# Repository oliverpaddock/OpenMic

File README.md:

# OpenMic
OpenMic is an open-source, 2-in, 2-out, usb-c audio interface.

## About

### Why open source?
Open source audio/music hardware is not scarce, but general-purpose open source audio interfaces for musicians are essentially non-existent. OpenMic brings repairability, transparency, and education to an overlooked corner of music hardware.

You own your hardware. All schematics, firmware, and design files are publicly accessible so you can repair it, modify it, and understand it.

### What is OpenMic?
If you aren't familiar with audio interfaces like the [Focusrite Scarlett 2i2](https://us.focusrite.com/products/scarlett-2i2) or the [Universal Audio Apollo Twin](https://www.uaudio.com/products/apollo-twin-x), they basically take analog audio - from a microphone, a guitar, a synth, etc. - and convert it into digital audio your computer can use in a DAW like Ableton, Logic, or Audacity. They also convert digital audio from your computer back into analog audio that you can hear through speakers or headphones. Interfaces also typically provide some sort of amplification or volume control on the inputs and outputs.

This is exactly what OpenMic does. Two inputs that can take microphone/line/instrument level signals, outputs for your speakers, and a headphone jack. Plus a few other features like phantom power that are listed in more detail in the [Features](#features) section.

*System block diagram*

## Current Status
OpenMic is currently in the prototyping stage. The circuit has been designed and [simulated](hardware/sims/), and individual systems are being built and tested. View the [schematics](docs/schematics/openmic.pdf) to see the current circuit design.

Progress will be posted on the [OpenMic blog](https://olpad.codeberg.page/openmic-blog) as prototyping continues.

### Roadmap
- [x] Initial design and component selection
- [x] Simulation for design verification
- [ ] Subsystem prototyping
- [ ] Full board design in KiCad
- [ ] First full v1 board
- [ ] Crowd supply launch
- [ ] Production

## Features
- 2 combo XLR/TRS inputs (mic/line/inst)
- Balanced TRS stereo line outputs
- TRS headphone output
- 48V phantom power
- Direct monitoring
- Up to 32-bit/96kHz
- USB-C bus powered (1.5A) with external USB-C fallback
- Drives headphones from 32Ω to 600Ω
- Fully open hardware and firmware

## Getting Started
If you want to view/edit KiCAD files, make sure to add the part libraries located in /hardware/libs to your project or globally in your KiCAD instance.

---

### Sponsors

&emsp;

&emsp;

### Special Thanks

THAT Corporation

Neutrik

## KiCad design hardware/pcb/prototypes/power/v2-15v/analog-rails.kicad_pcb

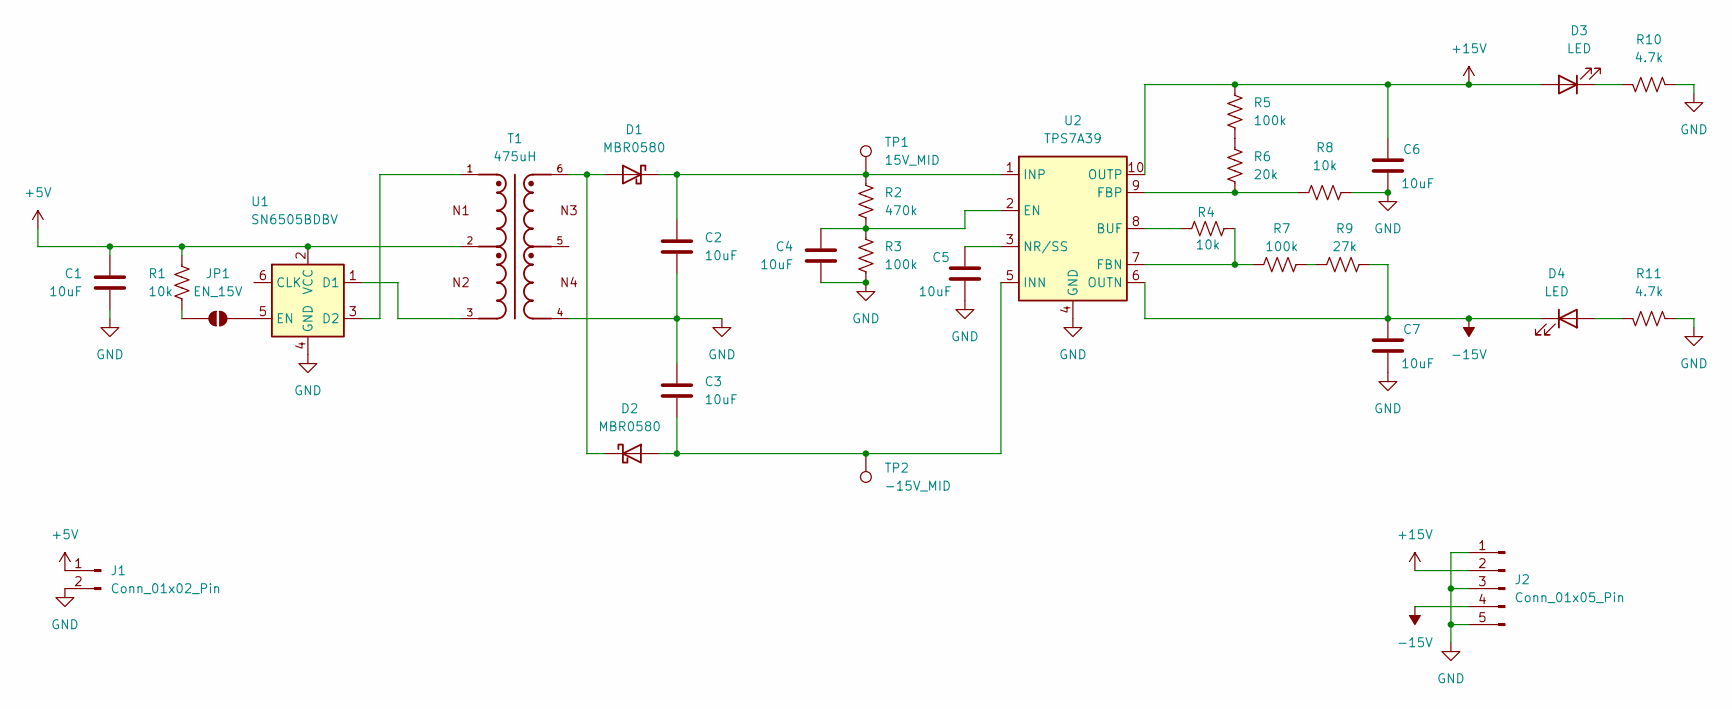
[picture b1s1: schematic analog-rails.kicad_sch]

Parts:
C1, C5: 10uF; C_0805_2012Metric_Pad1.18x1.45mm_HandSolder; Voltage 10; MPN CL21A106KAYNNNE; LCSC C15850
C2, C3, C4, C6, C7: 10uF; C_0805_2012Metric_Pad1.18x1.45mm_HandSolder; Voltage 50; MPN CL21A106KAYNNNE; LCSC C15850
D1, D2: MBR0580; D_SOD-123; MPN MBR0580; LCSC C77339
D3, D4: LED; LED_0805_2012Metric_Pad1.15x1.40mm_HandSolder
J1: Conn_01x02_Pin; PinHeader_1x02_P2.54mm_Vertical
J2: Conn_01x05_Pin; PinHeader_1x05_P2.54mm_Vertical
JP1: EN_15V; SolderJumper-2_P1.3mm_Open_RoundedPad1.0x1.5mm
R1, R4, R8: 10k; R_0805_2012Metric_Pad1.20x1.40mm_HandSolder; MPN 0805W8F1002T5E; LCSC C17414
R2: 470k; R_0805_2012Metric_Pad1.20x1.40mm_HandSolder; MPN 0805W8F4700T5E; LCSC C17710
R3, R5, R7: 100k; R_0805_2012Metric_Pad1.20x1.40mm_HandSolder; MPN 0805W8F1003T5E; LCSC C149504
R6: 20k; R_0805_2012Metric_Pad1.20x1.40mm_HandSolder; MPN 0805W8F2002T5E; LCSC C4328
R9: 27k; R_0805_2012Metric_Pad1.20x1.40mm_HandSolder; MPN 0805W8F2702T5E; LCSC C17593
R10, R11: 4.7k; R_0805_2012Metric_Pad1.20x1.40mm_HandSolder; MPN 0805W8F1003T5E; LCSC C149504
T1: 475uH; Wurth Elektronik 760390015; MPN 760390015; LCSC C249186
TP1: 15V_MID; TestPoint_Pad_1.0x1.0mm
TP2: -15V_MID; TestPoint_Pad_1.0x1.0mm
U1: SN6505BDBV; SOT-23-6; MPN SN6505BDBVR; LCSC C74518
U2: TPS7A39; Texas_S-PVSON-N10_ThermalVias; MPN TPS7A3901DSCR; LCSC C2685819

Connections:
+5V: C1.1, J1.1, R1.2, T1.2, U1.2 (VCC)
+15V: C6.1, D3.2 (A), J2.2, R5.1, U2.10 (OUTP)
-15V: C7.1, D4.1 (K), J2.4, R9.2, U2.6 (OUTN)
GND: C1.2, C2.2, C3.1, C4.2, C5.2, C6.2, C7.2, J1.2, J2.1, J2.3, J2.5, R3.2, R8.2, R10.1, R11.1, T1.4, U1.4 (GND), U2.4 (GND), U2.11 (GND)
unnamed: D1.2 (A), D2.1 (K), T1.6
unnamed: C2.1, D1.1 (K), R2.1, TP1.1 (1_1), U2.1 (INP)
unnamed: C3.2, D2.2 (A), TP2.1 (1_1), U2.5 (INN)
unnamed: D3.1 (K), R10.2
unnamed: D4.2 (A), R11.2
unnamed: JP1.1 (A), R1.1
unnamed: JP1.2 (B), U1.5 (EN)
unnamed: R5.2, R6.1
unnamed: R7.2, R9.1
unnamed: T1.3, U1.1 (D1)
unnamed: T1.1, U1.3 (D2)
unnamed: R4.1, U2.8 (BUF)
unnamed: C4.1, R2.2, R3.1, U2.2 (EN)
unnamed: R4.2, R7.1, U2.7 (FBN)
unnamed: R6.2, R8.1, U2.9 (FBP)
unnamed: C5.1, U2.3 (NR/SS)

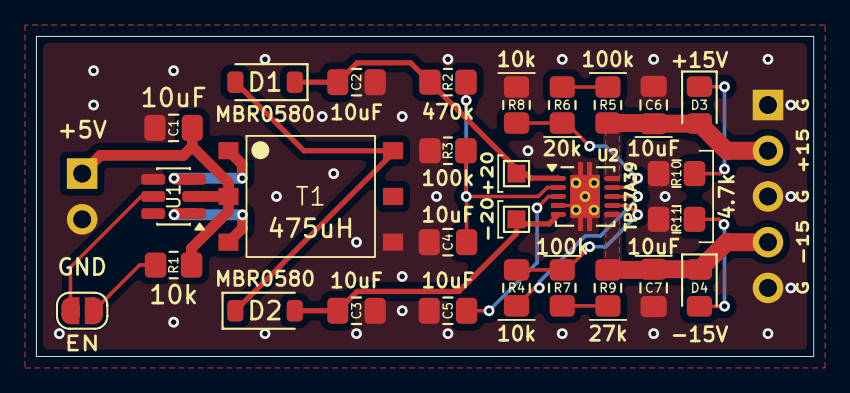
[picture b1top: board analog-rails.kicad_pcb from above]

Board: 2 copper layers, 43.2 x 17.8 mm, 30 parts (0 on the bottom side), 20 nets.

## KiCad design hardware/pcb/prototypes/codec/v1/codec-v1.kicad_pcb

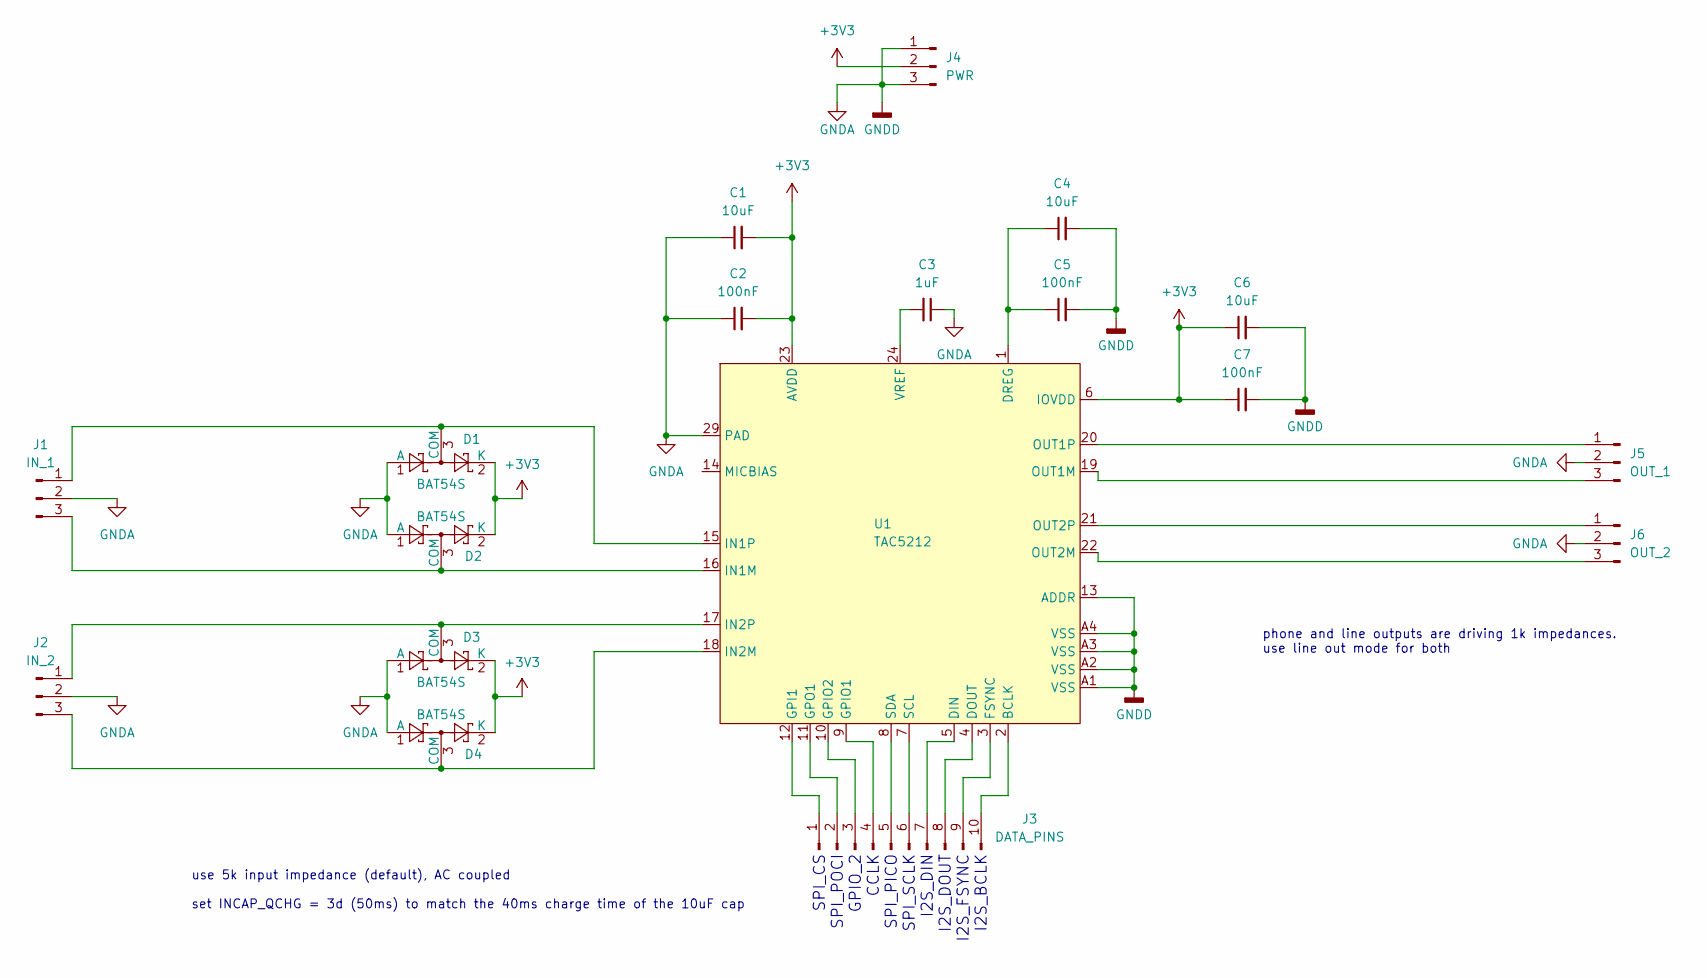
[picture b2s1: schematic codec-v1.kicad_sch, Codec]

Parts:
C1, C4, C6: 10uF; C_0805_2012Metric
C2, C5, C7: 100nF; C_0805_2012Metric
C3: 1uF; C_0805_2012Metric
D1, D2, D3, D4: BAT54S; SOT-23
J1: IN_1; PinHeader_1x03_P2.54mm_Vertical
J2: IN_2; PinHeader_1x03_P2.54mm_Vertical
J3: DATA_PINS; PinHeader_1x10_P2.54mm_Vertical
J4: PWR; PinHeader_1x03_P2.54mm_Vertical
J5: OUT_1; PinHeader_1x03_P2.54mm_Vertical
J6: OUT_2; PinHeader_1x03_P2.54mm_Vertical
U1: TAC5212

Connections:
+3V3: C1.2, C2.2, C6.1, C7.1, D1.2 (K), D2.2 (K), D3.2 (K), D4.2 (K), J4.2, U1.6 (IOVDD), U1.23 (AVDD)
GNDA: C1.1, C2.1, C3.1, C4.2, C5.2, C6.2, C7.2, D1.1 (A), D2.1 (A), D3.1 (A), D4.1 (A), J1.2, J2.2, J4.1, J4.3, J5.2, J6.2, U1.13 (ADDR), U1.29 (PAD), U1.A1 (VSS), U1.A2 (VSS), U1.A3 (VSS), U1.A4 (VSS)
unnamed: D1.3 (COM), J1.1, U1.15 (IN1P)
unnamed: D2.3 (COM), J1.3, U1.16 (IN1M)
unnamed: D3.3 (COM), J2.1, U1.17 (IN2P)
unnamed: D4.3 (COM), J2.3, U1.18 (IN2M)
unnamed: J3.1, U1.12 (GPI1)
unnamed: J3.2, U1.11 (GPO1)
unnamed: J3.3, U1.10 (GPIO2)
unnamed: J3.4, U1.9 (GPIO1)
unnamed: J3.5, U1.8 (SDA)
unnamed: J3.6, U1.7 (SCL)
unnamed: J3.7, U1.5 (DIN)
unnamed: J3.8, U1.4 (DOUT)
unnamed: J3.9, U1.3 (FSYNC)
unnamed: J3.10, U1.2 (BCLK)
unnamed: J5.1, U1.20 (OUT1P)
unnamed: J5.3, U1.19 (OUT1M)
unnamed: J6.1, U1.21 (OUT2P)
unnamed: J6.3, U1.22 (OUT2M)
unnamed: C4.1, C5.1, U1.1 (DREG)
unnamed: C3.2, U1.24 (VREF)

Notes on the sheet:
phone and line outputs are driving 1k impedances. use line out mode for both
SPI_CS SPI_POCI GPIO_2 CCLK SPI_PICO SPI_SCLK I2S_DIN I2S_DOUT I2S_FSYNC I2S_BCLK
use 5k input impedance (default), AC coupled set INCAP_QCHG = 3d (50ms) to match the 40ms charge time of the 10uF cap

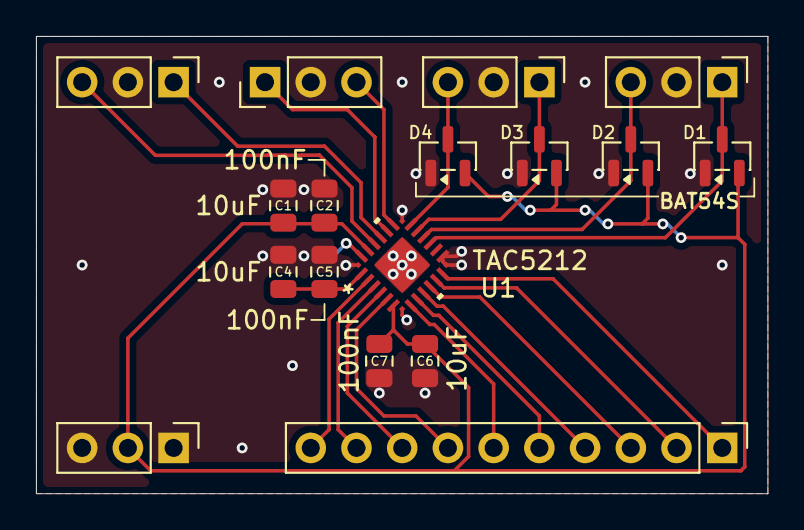
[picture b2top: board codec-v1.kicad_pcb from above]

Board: 2 copper layers, 40.6 x 25.4 mm, 18 parts (1 on the bottom side), 22 nets.

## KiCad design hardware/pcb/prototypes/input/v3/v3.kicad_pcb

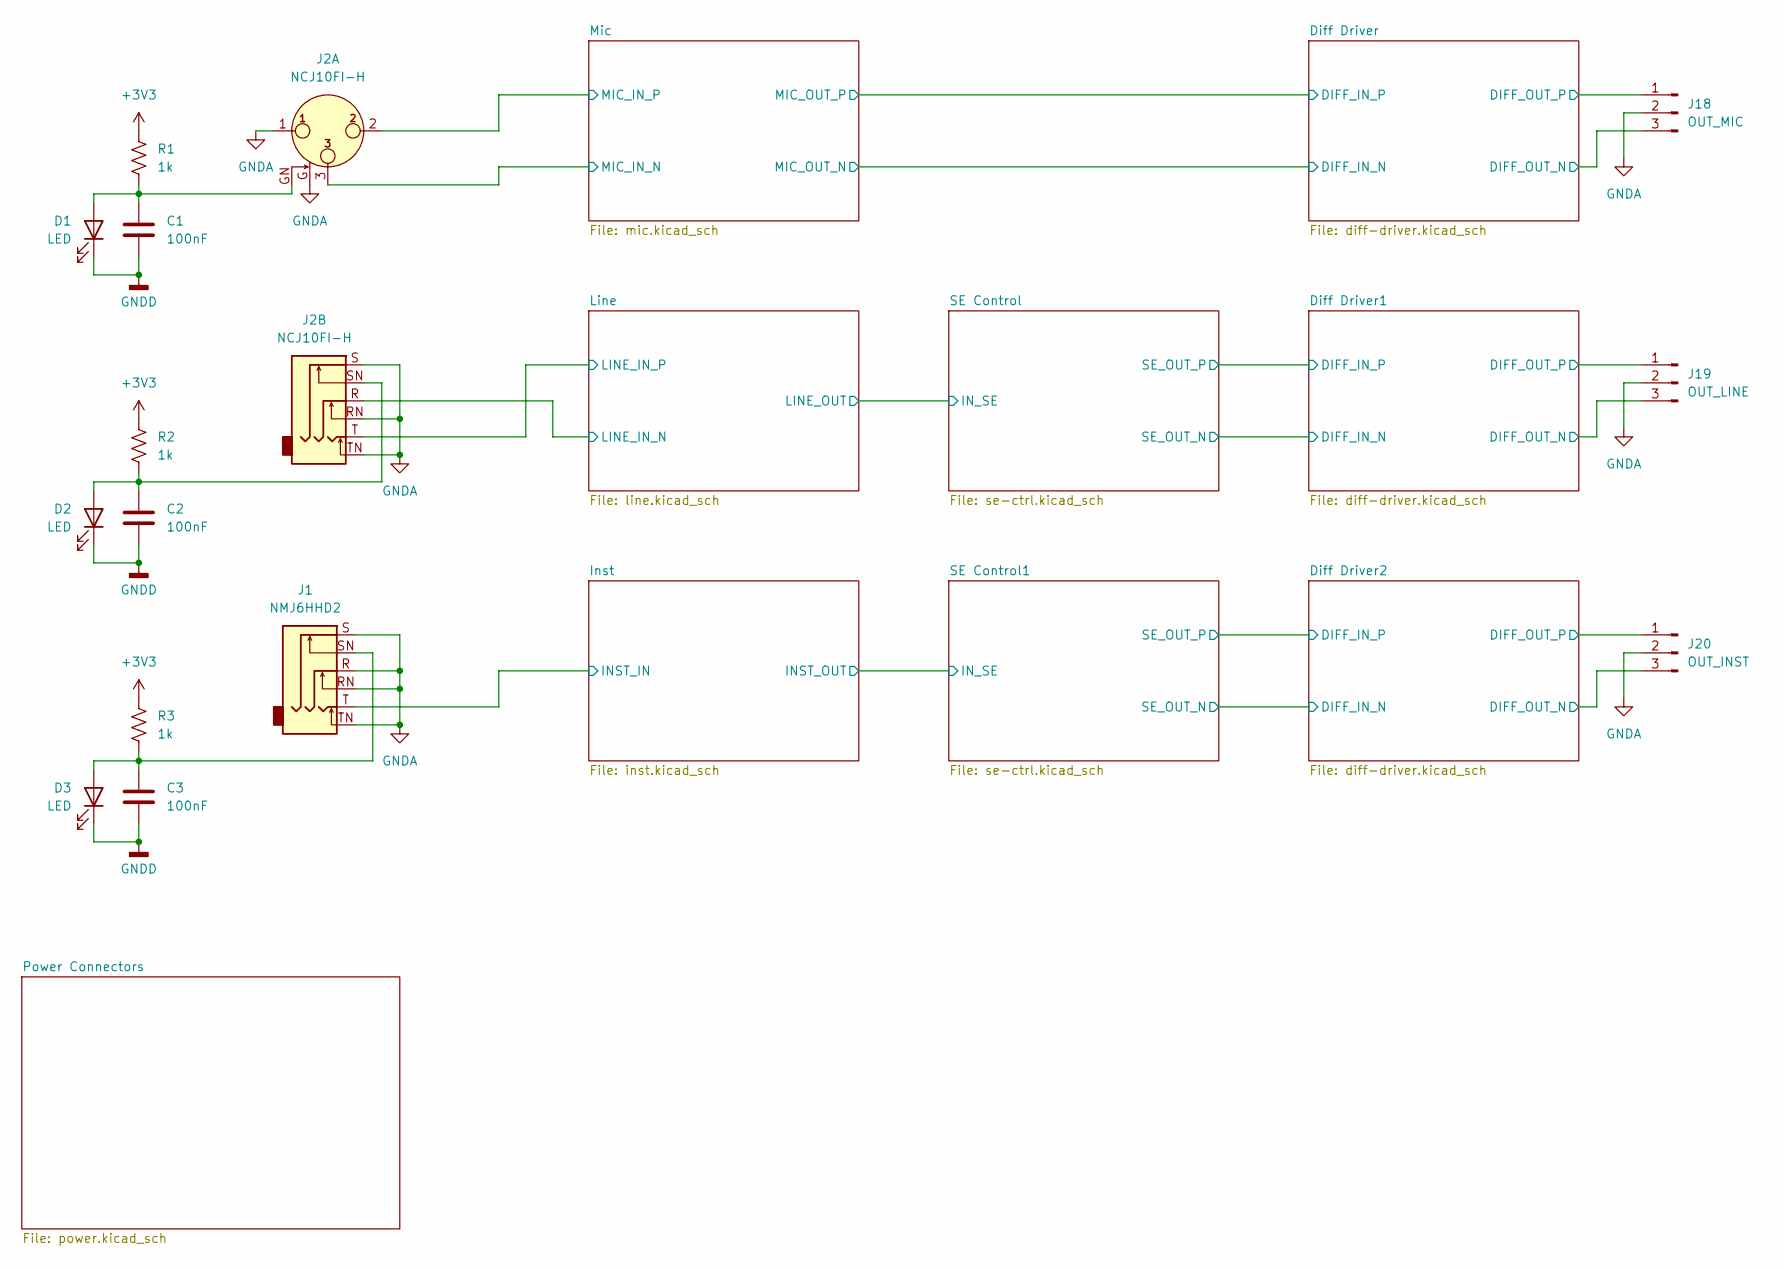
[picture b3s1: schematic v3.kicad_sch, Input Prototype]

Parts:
C1, C2, C3: 100nF; C_0805_2012Metric_Pad1.18x1.45mm_HandSolder; Voltage 6
D1, D2, D3: LED; LED_0805_2012Metric_Pad1.15x1.40mm_HandSolder
J1: NMJ6HHD2; Jack_6.35mm_Neutrik_NMJ6HHD2_Horizontal
J2: NCJ10FI-H; Jack_XLR-6.35mm_Neutrik_NCJ10FI-H_Horizontal
J18: OUT_MIC; PinHeader_1x03_P2.54mm_Vertical
J19: OUT_LINE; PinHeader_1x03_P2.54mm_Vertical
J20: OUT_INST; PinHeader_1x03_P2.54mm_Vertical
R1, R2, R3: 1k; R_0805_2012Metric_Pad1.20x1.40mm_HandSolder

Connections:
+3V3: R1.1, R2.1, R3.1; also elsewhere on the board
/Diff Driver1/DIFF_OUT_N: J19.3; also elsewhere on the board
/Diff Driver1/DIFF_OUT_P: J19.1; also elsewhere on the board
/Diff Driver2/DIFF_OUT_N: J20.3; also elsewhere on the board
/Diff Driver2/DIFF_OUT_P: J20.1; also elsewhere on the board
/Diff Driver/DIFF_OUT_N: J18.3; also elsewhere on the board
/Diff Driver/DIFF_OUT_P: J18.1; also elsewhere on the board
/Inst/INST_IN: J1.T; also elsewhere on the board
/Line/LINE_IN_N: J2.R; also elsewhere on the board
/Line/LINE_IN_P: J2.T; also elsewhere on the board
/Mic/MIC_IN_N: J2.3; also elsewhere on the board
/Mic/MIC_IN_P: J2.2; also elsewhere on the board
Earth: C1.2, C2.2, C3.2, D1.1 (K), D2.1 (K), D3.1 (K), J1.R, J1.RN, J1.S, J1.TN, J2.1, J2.G, J2.RN, J2.S, J2.TN, J18.2, J19.2, J20.2; also elsewhere on the board
unnamed: C1.1, D1.2 (A), J2.GN, R1.2
unnamed: C2.1, D2.2 (A), J2.SN, R2.2
unnamed: C3.1, D3.2 (A), J1.SN, R3.2

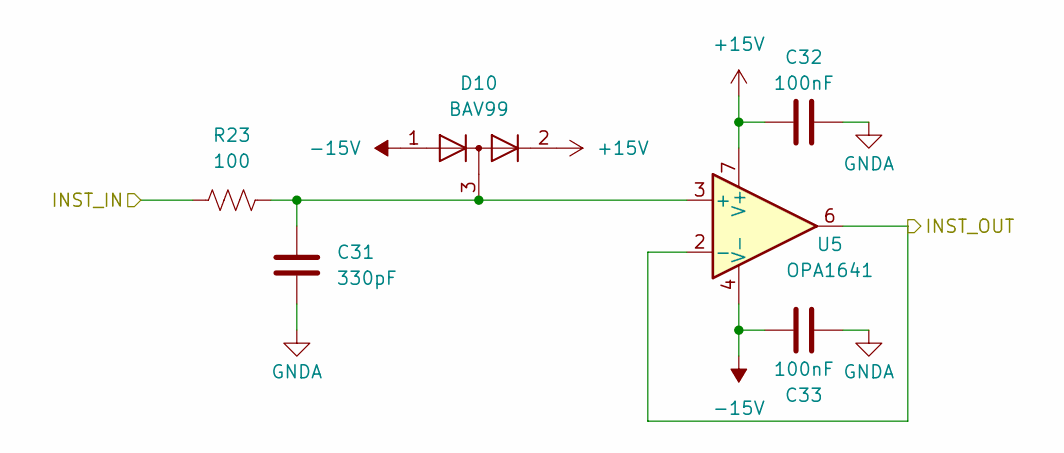
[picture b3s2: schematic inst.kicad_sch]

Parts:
C31: 330pF; C_0805_2012Metric_Pad1.18x1.45mm_HandSolder; Voltage 6
C32, C33: 100nF; C_0805_2012Metric_Pad1.18x1.45mm_HandSolder; Voltage 50
D10: BAV99; SOT-23
R23: 100; R_0805_2012Metric_Pad1.20x1.40mm_HandSolder
U5: OPA1641; SOIC-8_3.9x4.9mm_P1.27mm

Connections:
+15V: C32.2, D10.2 (A), U5.7 (V+); also elsewhere on the board
-15V: C33.2, D10.1 (K), U5.4 (V-); also elsewhere on the board
/Inst/INST_IN: R23.2; also elsewhere on the board
/Inst/INST_OUT: U5.2 (-), U5.6; also elsewhere on the board
Earth: C31.2, C32.1, C33.1; also elsewhere on the board
unnamed: C31.1, D10.3 (K), R23.1, U5.3 (+)

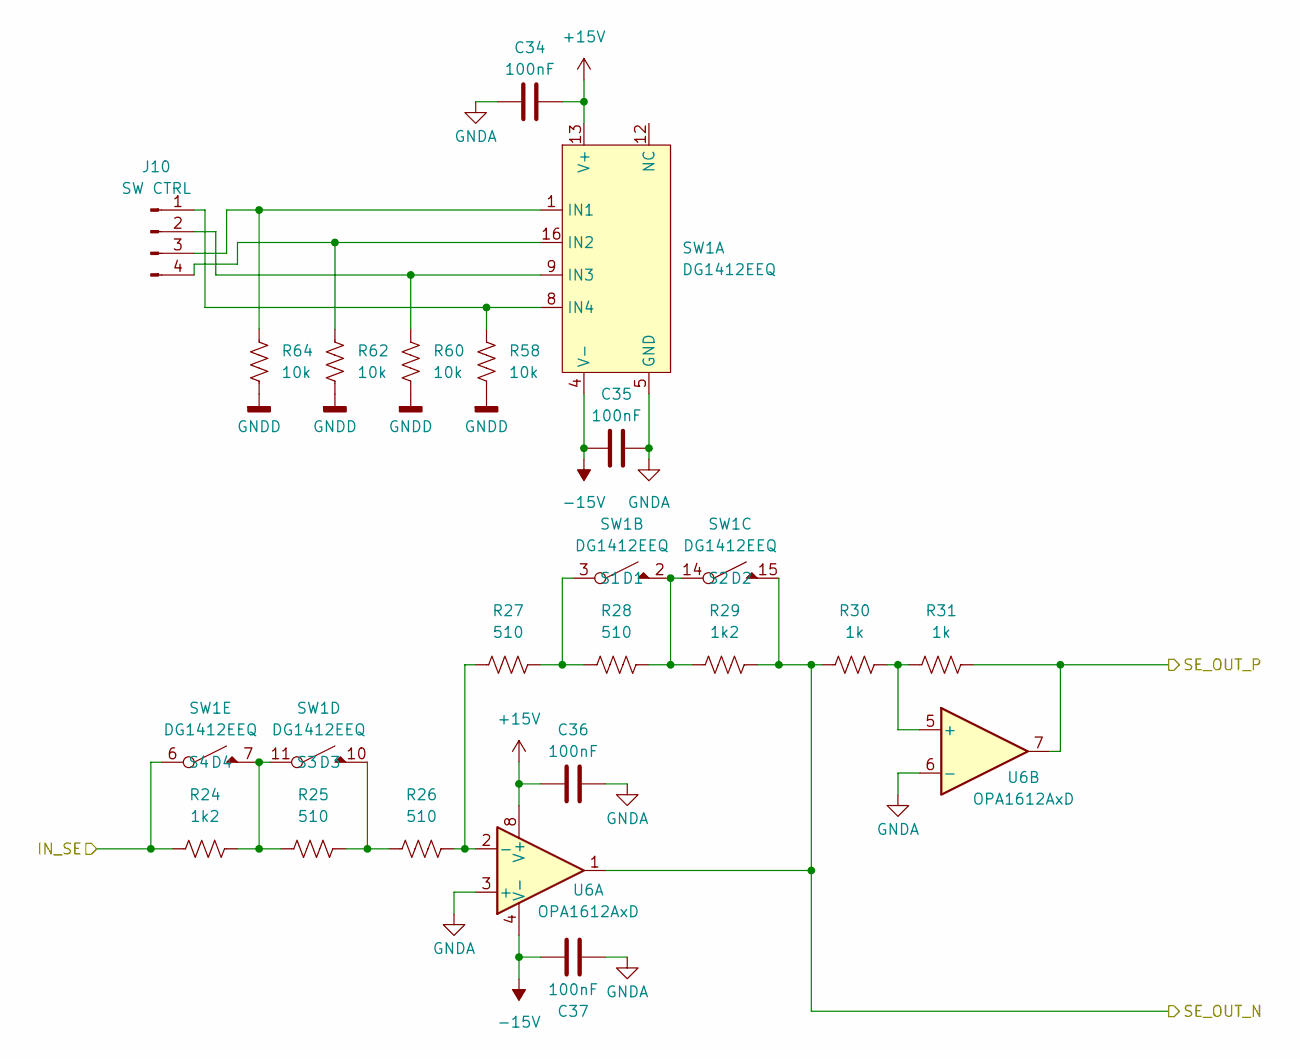
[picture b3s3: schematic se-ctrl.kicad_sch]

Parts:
C34, C35, C36, C37: 100nF; C_0805_2012Metric_Pad1.18x1.45mm_HandSolder; Voltage 50
J10: SW CTRL; PinHeader_1x04_P2.54mm_Vertical
R24, R29: 1k2; R_0805_2012Metric_Pad1.20x1.40mm_HandSolder
R25, R26, R27, R28: 510; R_0805_2012Metric_Pad1.20x1.40mm_HandSolder
R30, R31: 1k; R_0805_2012Metric_Pad1.20x1.40mm_HandSolder
R58, R60, R62, R64: 10k; R_0805_2012Metric_Pad1.20x1.40mm_HandSolder
SW1: DG1412EEQ; TSSOP-16_4.4x5mm_P0.65mm
U6: OPA1612AxD; SOIC-8_3.9x4.9mm_P1.27mm

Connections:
+15V: C34.2, C36.2, SW1.13 (V+), U6.8 (V+); also elsewhere on the board
-15V: C35.2, C37.2, SW1.4 (V-), U6.4 (V-); also elsewhere on the board
/Diff Driver1/DIFF_IN_N: R29.1, R30.2, SW1.15 (D2), U6.1; also elsewhere on the board
/Diff Driver1/DIFF_IN_P: R31.1, U6.7; also elsewhere on the board
/Line/LINE_OUT: R24.2, SW1.6 (S4); also elsewhere on the board
Earth: C34.1, C35.1, C36.1, C37.1, R58.2, R60.2, R62.2, R64.2, SW1.5 (GND), U6.3 (+), U6.6 (-); also elsewhere on the board
unnamed: J10.1, R58.1, SW1.8 (IN4)
unnamed: J10.2, R60.1, SW1.9 (IN3)
unnamed: J10.3, R64.1, SW1.1 (IN1)
unnamed: J10.4, R62.1, SW1.16 (IN2)
unnamed: R28.1, R29.2, SW1.2 (D1), SW1.14 (S2)
unnamed: R27.1, R28.2, SW1.3 (S1)
unnamed: R25.1, R26.2, SW1.10 (D3)
unnamed: R24.1, R25.2, SW1.7 (D4), SW1.11 (S3)
unnamed: R26.1, R27.2, U6.2 (-)
unnamed: R30.1, R31.2, U6.5 (+)

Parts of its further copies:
C38, C39, C40, C41: 100nF; C_0805_2012Metric_Pad1.18x1.45mm_HandSolder; Voltage 50
J11: SW CTRL; PinHeader_1x04_P2.54mm_Vertical
R32, R37: 1k2; R_0805_2012Metric_Pad1.20x1.40mm_HandSolder
R33, R34, R35, R36: 510; R_0805_2012Metric_Pad1.20x1.40mm_HandSolder
R38, R39: 1k; R_0805_2012Metric_Pad1.20x1.40mm_HandSolder
R59, R61, R63, R65: 10k; R_0805_2012Metric_Pad1.20x1.40mm_HandSolder
SW2: DG1412EEQ; TSSOP-16_4.4x5mm_P0.65mm
U7: OPA1612AxD; SOIC-8_3.9x4.9mm_P1.27mm

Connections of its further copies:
+15V: C38.2, C40.2, SW2.13 (V+), U7.8 (V+); also elsewhere on the board
-15V: C39.2, C41.2, SW2.4 (V-), U7.4 (V-); also elsewhere on the board
/Diff Driver2/DIFF_IN_N: R37.1, R38.2, SW2.15 (D2), U7.1; also elsewhere on the board
/Diff Driver2/DIFF_IN_P: R39.1, U7.7; also elsewhere on the board
/Inst/INST_OUT: R32.2, SW2.6 (S4); also elsewhere on the board
Earth: C38.1, C39.1, C40.1, C41.1, R59.2, R61.2, R63.2, R65.2, SW2.5 (GND), U7.3 (+), U7.6 (-); also elsewhere on the board
unnamed: J11.1, R59.1, SW2.8 (IN4)
unnamed: J11.2, R61.1, SW2.9 (IN3)
unnamed: J11.3, R65.1, SW2.1 (IN1)
unnamed: J11.4, R63.1, SW2.16 (IN2)
unnamed: R36.1, R37.2, SW2.2 (D1), SW2.14 (S2)
unnamed: R35.1, R36.2, SW2.3 (S1)
unnamed: R33.1, R34.2, SW2.10 (D3)
unnamed: R32.1, R33.2, SW2.7 (D4), SW2.11 (S3)
unnamed: R34.1, R35.2, U7.2 (-)
unnamed: R38.1, R39.2, U7.5 (+)

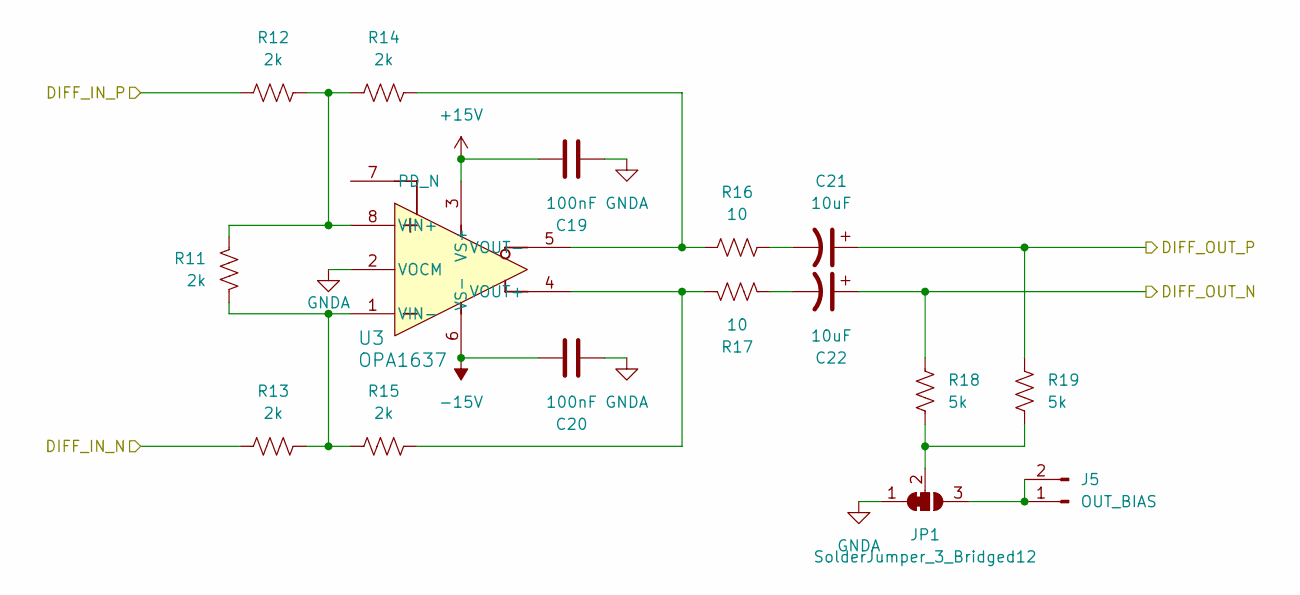
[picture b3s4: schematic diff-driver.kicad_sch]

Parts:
C19, C20: 100nF; C_0805_2012Metric_Pad1.18x1.45mm_HandSolder; Voltage 6
C21, C22: 10uF; C_Radial_D5.0mm_H11.0mm_P2.00mm; Voltage 50
J5: OUT_BIAS; PinHeader_1x02_P2.54mm_Vertical
JP1: SolderJumper_3_Bridged12; SolderJumper-3_P1.3mm_Bridged12_RoundedPad1.0x1.5mm
R11, R12, R13, R14, R15: 2k; R_0805_2012Metric_Pad1.20x1.40mm_HandSolder
R16, R17: 10; R_0805_2012Metric_Pad1.20x1.40mm_HandSolder
R18, R19: 5k; R_0805_2012Metric_Pad1.20x1.40mm_HandSolder
U3: OPA1637; VSSOP-8_3x3mm_P0.65mm

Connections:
+15V: C19.1, U3.3 (VS+); also elsewhere on the board
-15V: C20.1, U3.6 (VS-); also elsewhere on the board
/Diff Driver/DIFF_IN_N: R13.1; also elsewhere on the board
/Diff Driver/DIFF_IN_P: R12.1; also elsewhere on the board
/Diff Driver/DIFF_OUT_N: C22.1, R18.2; also elsewhere on the board
/Diff Driver/DIFF_OUT_P: C21.1, R19.2; also elsewhere on the board
Earth: C19.2, C20.2, JP1.1 (A), U3.2 (VOCM); also elsewhere on the board
unnamed: C21.2, R16.2
unnamed: C22.2, R17.2
unnamed: J5.1, J5.2, JP1.3 (B)
unnamed: JP1.2 (C), R18.1, R19.1
unnamed: R11.2, R12.2, R14.1, U3.8 (VIN+)
unnamed: R11.1, R13.2, R15.1, U3.1 (VIN-)
unnamed: R15.2, R17.1, U3.4 (VOUT+)
unnamed: R14.2, R16.1, U3.5 (VOUT-)

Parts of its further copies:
C42, C43, C46, C47: 100nF; C_0805_2012Metric_Pad1.18x1.45mm_HandSolder; Voltage 6
C44, C45, C48, C49: 10uF; C_Radial_D5.0mm_H11.0mm_P2.00mm; Voltage 50
J12, J13: OUT_BIAS; PinHeader_1x02_P2.54mm_Vertical
JP2, JP3: SolderJumper_3_Bridged12; SolderJumper-3_P1.3mm_Bridged12_RoundedPad1.0x1.5mm
R40, R41, R42, R43, R44, R49, R50, R51, R52, R53: 2k; R_0805_2012Metric_Pad1.20x1.40mm_HandSolder
R45, R46, R54, R55: 10; R_0805_2012Metric_Pad1.20x1.40mm_HandSolder
R47, R48, R56, R57: 5k; R_0805_2012Metric_Pad1.20x1.40mm_HandSolder
U8, U9: OPA1637; VSSOP-8_3x3mm_P0.65mm

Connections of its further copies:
+15V: C42.1, C46.1, U8.3 (VS+), U9.3 (VS+); also elsewhere on the board
-15V: C43.1, C47.1, U8.6 (VS-), U9.6 (VS-); also elsewhere on the board
/Diff Driver1/DIFF_IN_N: R42.1; also elsewhere on the board
/Diff Driver1/DIFF_IN_P: R41.1; also elsewhere on the board
/Diff Driver1/DIFF_OUT_N: C45.1, R47.2; also elsewhere on the board
/Diff Driver1/DIFF_OUT_P: C44.1, R48.2; also elsewhere on the board
/Diff Driver2/DIFF_IN_N: R51.1; also elsewhere on the board
/Diff Driver2/DIFF_IN_P: R50.1; also elsewhere on the board
/Diff Driver2/DIFF_OUT_N: C49.1, R56.2; also elsewhere on the board
/Diff Driver2/DIFF_OUT_P: C48.1, R57.2; also elsewhere on the board
Earth: C42.2, C43.2, C46.2, C47.2, JP2.1 (A), JP3.1 (A), U8.2 (VOCM), U9.2 (VOCM); also elsewhere on the board
unnamed: C44.2, R45.2
unnamed: C45.2, R46.2
unnamed: C48.2, R54.2
unnamed: C49.2, R55.2
unnamed: J12.1, J12.2, JP2.3 (B)
unnamed: J13.1, J13.2, JP3.3 (B)
unnamed: JP2.2 (C), R47.1, R48.1
unnamed: JP3.2 (C), R56.1, R57.1
unnamed: R40.2, R41.2, R43.1, U8.8 (VIN+)
unnamed: R40.1, R42.2, R44.1, U8.1 (VIN-)
unnamed: R44.2, R46.1, U8.4 (VOUT+)
unnamed: R43.2, R45.1, U8.5 (VOUT-)
unnamed: R49.2, R50.2, R52.1, U9.8 (VIN+)
unnamed: R49.1, R51.2, R53.1, U9.1 (VIN-)
unnamed: R53.2, R55.1, U9.4 (VOUT+)
unnamed: R52.2, R54.1, U9.5 (VOUT-)

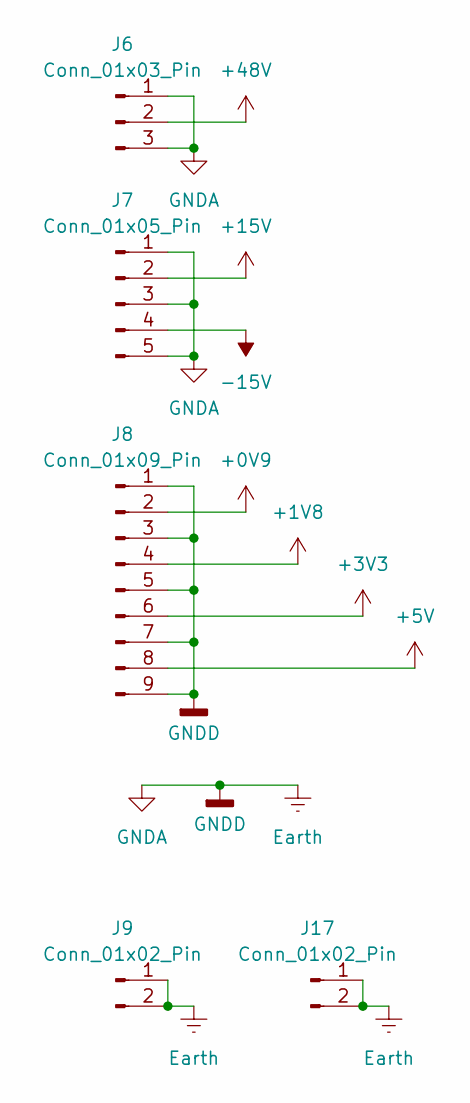
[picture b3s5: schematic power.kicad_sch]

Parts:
J6: Conn_01x03_Pin; PinHeader_1x03_P2.54mm_Vertical
J7: Conn_01x05_Pin; PinHeader_1x05_P2.54mm_Vertical
J8: Conn_01x09_Pin; PinHeader_1x09_P2.54mm_Vertical
J9, J17: Conn_01x02_Pin; PinHeader_1x02_P2.54mm_Vertical

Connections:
+0V9: J8.2
+1V8: J8.4
+3V3: J8.6; also elsewhere on the board
+5V: J8.8
+15V: J7.2; also elsewhere on the board
+48V: J6.2; also elsewhere on the board
-15V: J7.4; also elsewhere on the board
Earth: J6.1, J6.3, J7.1, J7.3, J7.5, J8.1, J8.3, J8.5, J8.7, J8.9, J9.1, J9.2, J17.1, J17.2; also elsewhere on the board

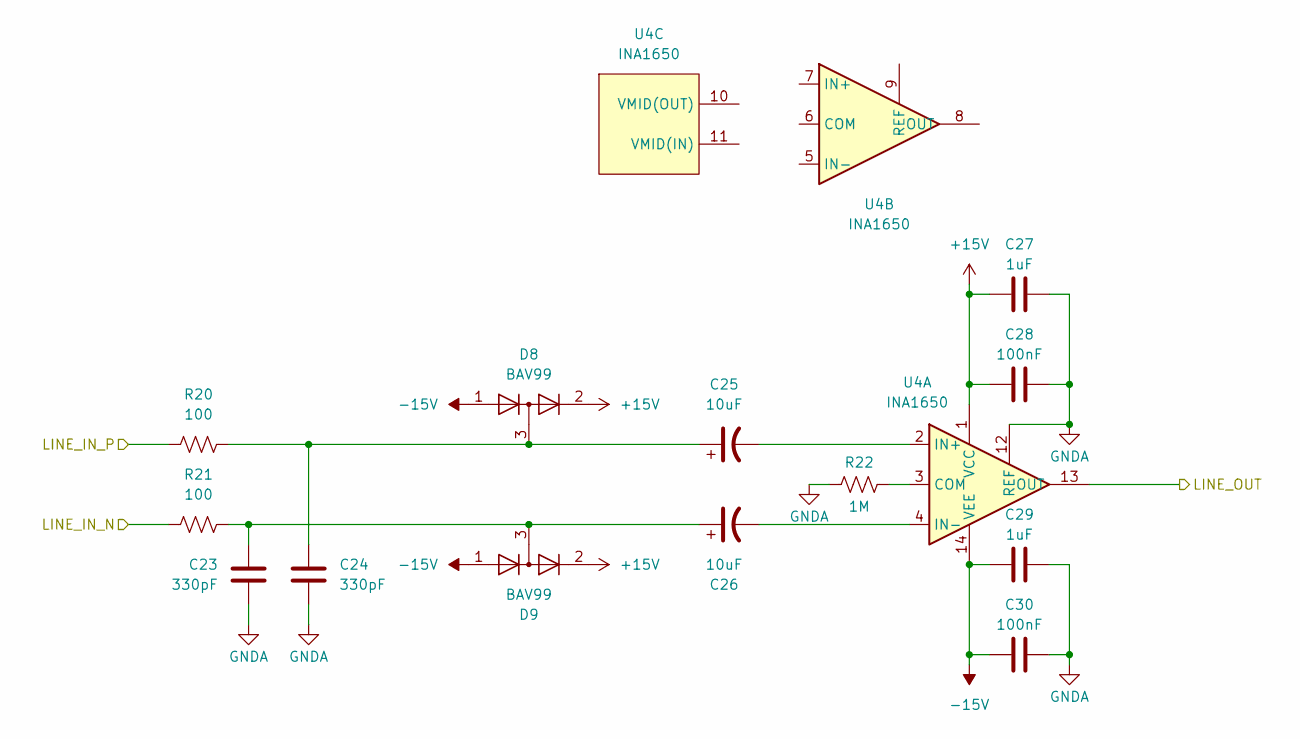
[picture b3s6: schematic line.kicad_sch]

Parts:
C23, C24: 330pF; C_0805_2012Metric_Pad1.18x1.45mm_HandSolder; Voltage 6
C25, C26: 10uF; C_Radial_D5.0mm_H11.0mm_P2.00mm; Voltage 50
C27, C29: 1uF; C_0805_2012Metric_Pad1.18x1.45mm_HandSolder; Voltage 50
C28, C30: 100nF; C_0805_2012Metric_Pad1.18x1.45mm_HandSolder; Voltage 50
D8, D9: BAV99; SOT-23
R20, R21: 100; R_0805_2012Metric_Pad1.20x1.40mm_HandSolder
R22: 1M; R_0805_2012Metric_Pad1.20x1.40mm_HandSolder
U4: INA1650; TSSOP-14_4.4x5mm_P0.65mm

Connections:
+15V: C27.2, C28.2, D8.2 (A), D9.2 (A), U4.1 (VCC); also elsewhere on the board
-15V: C29.2, C30.2, D8.1 (K), D9.1 (K), U4.14 (VEE); also elsewhere on the board
/Line/LINE_IN_N: R21.2; also elsewhere on the board
/Line/LINE_IN_P: R20.2; also elsewhere on the board
/Line/LINE_OUT: U4.13 (OUT); also elsewhere on the board
Earth: C23.2, C24.2, C27.1, C28.1, C29.1, C30.1, R22.1, U4.12 (REF); also elsewhere on the board
unnamed: C23.1, C26.1, D9.3 (K), R21.1
unnamed: C24.1, C25.1, D8.3 (K), R20.1
unnamed: R22.2, U4.3 (COM)
unnamed: C25.2, U4.2 (IN+)
unnamed: C26.2, U4.4 (IN-)

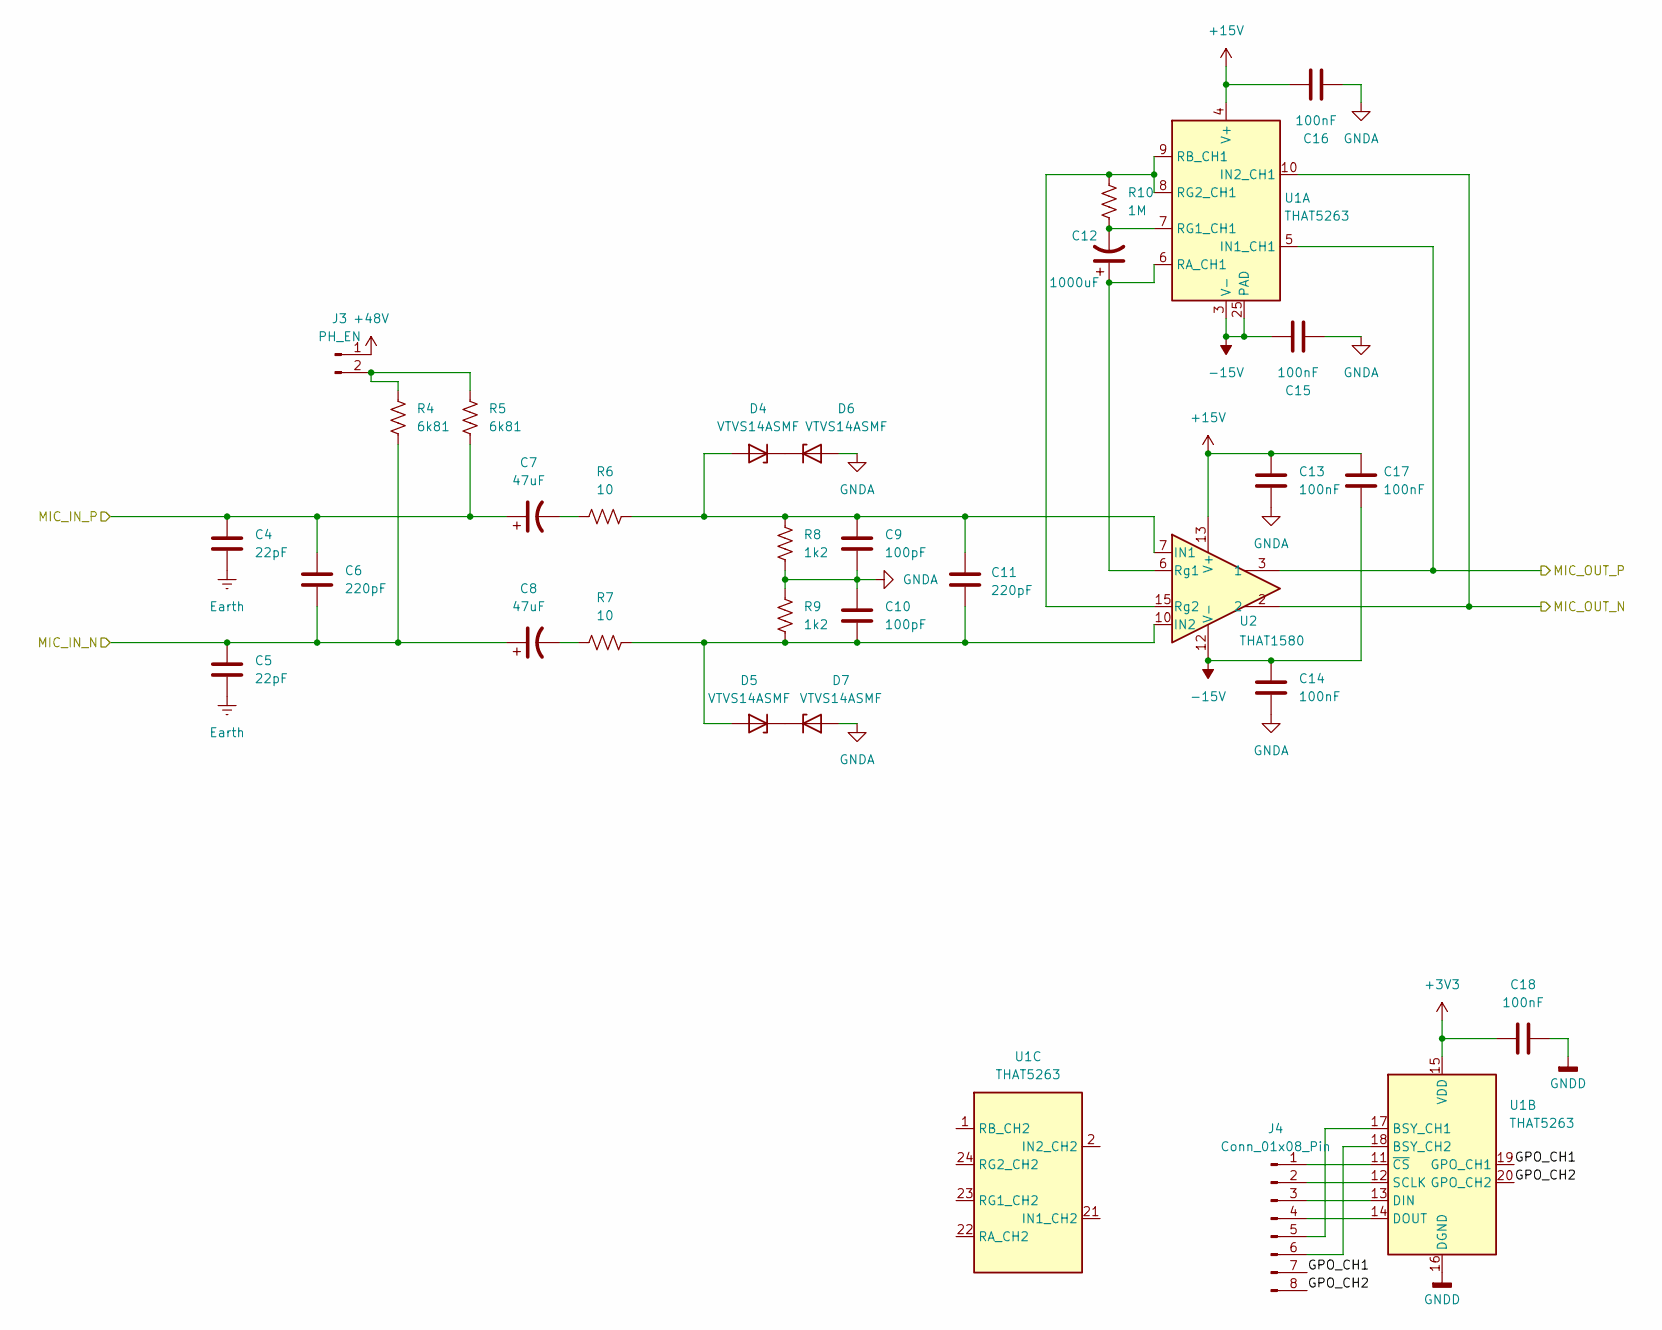
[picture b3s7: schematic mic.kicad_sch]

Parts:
C4, C5: 22pF; C_0805_2012Metric_Pad1.18x1.45mm_HandSolder; Voltage 50
C6, C11: 220pF; C_0805_2012Metric_Pad1.18x1.45mm_HandSolder; Voltage 50
C7, C8: 47uF; C_Radial_D10.0mm_H12.5mm_P5.00mm; Voltage 50
C9, C10: 100pF; C_0805_2012Metric_Pad1.18x1.45mm_HandSolder; Voltage 50
C12: 1000uF; CP_Radial_D8.0mm_P3.50mm; Voltage 6.3
C13, C14, C15, C16, C17, C18: 100nF; C_0805_2012Metric_Pad1.18x1.45mm_HandSolder; Voltage 6
D4, D5, D6, D7: VTVS14ASMF; D_SMF
J3: PH_EN; PinHeader_1x02_P2.54mm_Vertical
J4: Conn_01x08_Pin; PinHeader_1x08_P2.54mm_Vertical
R4, R5: 6k81; R_0805_2012Metric_Pad1.20x1.40mm_HandSolder
R6, R7: 10; R_0805_2012Metric_Pad1.20x1.40mm_HandSolder
R8, R9: 1k2; R_0805_2012Metric_Pad1.20x1.40mm_HandSolder
R10: 1M; R_0805_2012Metric_Pad1.20x1.40mm_HandSolder
U1: THAT5263; QFN-24-1EP_5x5mm_P0.65mm_EP3.4x3.4mm
U2: THAT1580; QFN-16-1EP_4x4mm_P0.65mm_EP2.1x2.1mm_ThermalVias

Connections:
+3V3: C18.1, U1.15 (VDD); also elsewhere on the board
+15V: C13.1, C16.1, C17.1, U1.4 (V+), U2.13 (V+); also elsewhere on the board
+48V: J3.1; also elsewhere on the board
-15V: C14.1, C15.1, C17.2, U1.3 (V-), U1.25 (PAD), U2.12 (V-), U2.17 (V-); also elsewhere on the board
/Diff Driver/DIFF_IN_N: U1.10 (IN2_CH1), U2.2; also elsewhere on the board
/Diff Driver/DIFF_IN_P: U1.5 (IN1_CH1), U2.3 (1); also elsewhere on the board
/Mic/GPO_CH1: J4.7, U1.19 (GPO_CH1)
/Mic/GPO_CH2: J4.8, U1.20 (GPO_CH2)
/Mic/MIC_IN_N: C5.1, C6.2, C8.1, R4.2; also elsewhere on the board
/Mic/MIC_IN_P: C4.1, C6.1, C7.1, R5.2; also elsewhere on the board
Earth: C4.2, C5.2, C9.2, C10.1, C13.2, C14.2, C15.2, C16.2, C18.2, D6.2 (A), D7.2 (A), R8.1, R9.2, U1.16 (DGND); also elsewhere on the board
unnamed: C7.2, R6.1
unnamed: C8.2, R7.1
unnamed: C9.1, C11.1, D4.2 (A), R6.2, R8.2, U2.7 (IN1)
unnamed: D4.1 (K), D6.1 (K)
unnamed: C10.2, C11.2, D5.2 (A), R7.2, R9.1, U2.10 (IN2)
unnamed: D5.1 (K), D7.1 (K)
unnamed: J3.2, R4.1, R5.1
unnamed: J4.1, U1.11 (~CS)
unnamed: J4.2, U1.12 (SCLK)
unnamed: J4.3, U1.13 (DIN)
unnamed: J4.4, U1.14 (DOUT)
unnamed: J4.5, U1.17 (BSY_CH1)
unnamed: J4.6, U1.18 (BSY_CH2)
unnamed: C12.1, U1.6 (RA_CH1), U2.6 (Rg1)
unnamed: R10.2, U1.8 (RG2_CH1), U1.9 (RB_CH1), U2.15 (Rg2)
unnamed: C12.2, R10.1, U1.7 (RG1_CH1)
